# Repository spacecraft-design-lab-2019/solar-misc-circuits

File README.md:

# solar-misc-circuits
Circuit "blocks" for the energy harvesting, burn wire, photosensor, and FPC connector circuits

# ❗ not finished ❗

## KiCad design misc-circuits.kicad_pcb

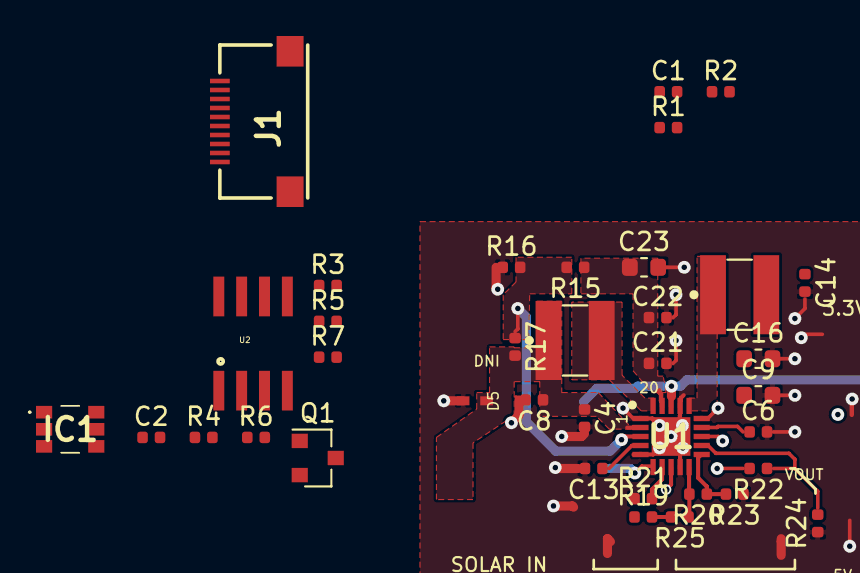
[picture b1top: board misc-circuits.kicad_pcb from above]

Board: 6 copper layers, 40 parts (0 on the bottom side), 23 nets.

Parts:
C1: 1.0uF; C_0402_1005Metric
C2, C6, C8, C17, C22: 0.1uF; C_0402_1005Metric
C4, C21: 4.7uF; C_0402_1005Metric
C9, C16, C19, C23: 100uF; C_0603_1608Metric
C13: 10nF; C_0402_1005Metric
C14: 22uF; C_0402_1005Metric
D5: BZT52C4V7t; SOD523
IC1: TSL2561
J1: XF2M-1015-1A
L1: 22uH-LPS4018-223MR; LPS4018
L4: 10uH-LPS4018-103MR; LPS4018
Q1: IRLML2803; SOT-23
R1, R2, R6, R7, R14, R15, R16, R17: 0; R_0402_1005Metric
R3: 10k; R_0402_1005Metric
R4: 4.7k; R_0402_1005Metric
R5: 100k; R_0402_1005Metric
R19: 7.32M; R_0402_1005Metric
R20, R22: 8.25M; R_0402_1005Metric
R21: 5.62M; R_0402_1005Metric
R23: 4.53M; R_0402_1005Metric
R24: 4.75M; R_0402_1005Metric
R25: 374K; R_0402_1005Metric
U1: Value; QFN50P350X350X100-21N-D
U2: NDS8434

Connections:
+3V3: C2.2, C6.1, C9.1, C14.1, C16.1, C17.1, IC1.1, J1.8, L4.2, R6.2, U1.14
/VBAT: C19.1, R14.2, U1.18
/VBURN: U2.5, U2.6, U2.7, U2.8
BATT_N: J1.4, R2.1
BATT_P: J1.2, R5.2, R14.1, U2.1, U2.2, U2.3
BURN1: R3.1, R4.2
GND: C1.2, C2.1, C4.2, C6.2, C8.2, C9.2, C13.2, C14.2, C16.2, C17.2, C19.2, C21.2, C22.2, C23.2, D5.A, IC1.3, J1.10, Q1.2, R2.2, R3.2, R7.1, R16.1, R21.1, R23.1, R24.1, U1.1, U1.5, U1.9, U1.15, U1.17, U1.21
unnamed: C13.1, U1.4
unnamed: C21.1, C22.1, C23.1, R15.1, U1.19
unnamed: IC1.2, R6.1, R7.2
unnamed: L1.2, U1.20
unnamed: L4.1, U1.16
unnamed: Q1.1, R4.1
unnamed: Q1.3, R5.1, U2.4
unnamed: R15.2, R16.2, R17.1, U1.3
unnamed: R19.1, R21.2, U1.7
unnamed: R19.2, R22.2, R25.2, U1.8
unnamed: R20.1, R23.2, U1.11
unnamed: R20.2, R25.1, U1.10
unnamed: R22.1, R24.2, U1.12
VBAT_OK: R1.1, U1.13
VOUT_EN: C1.1, R1.2, U1.6
VSOLAR: C4.1, C8.1, D5.C, L1.1, R17.2, U1.2

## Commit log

2019-10-23 inital commit of energy harvesting circuit
2019-10-23 moving layout over to 0402 size components and cleaning up
2019-10-23 added preliminary burn wire circuit, flat flex cable, and sun sensor *layout is not complete*
